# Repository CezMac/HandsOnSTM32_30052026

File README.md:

# HandsOnSTM32_30052026
Repozytorium dla uczestników

Ćwiczenie 0 - Jak używać STM32CubeProgrammera

Ćwiczenie 1 - Rozpoczęcie nowego projektu i implementacja printf()

Ćwiczenie 2 - Projekt zegarka binarnego

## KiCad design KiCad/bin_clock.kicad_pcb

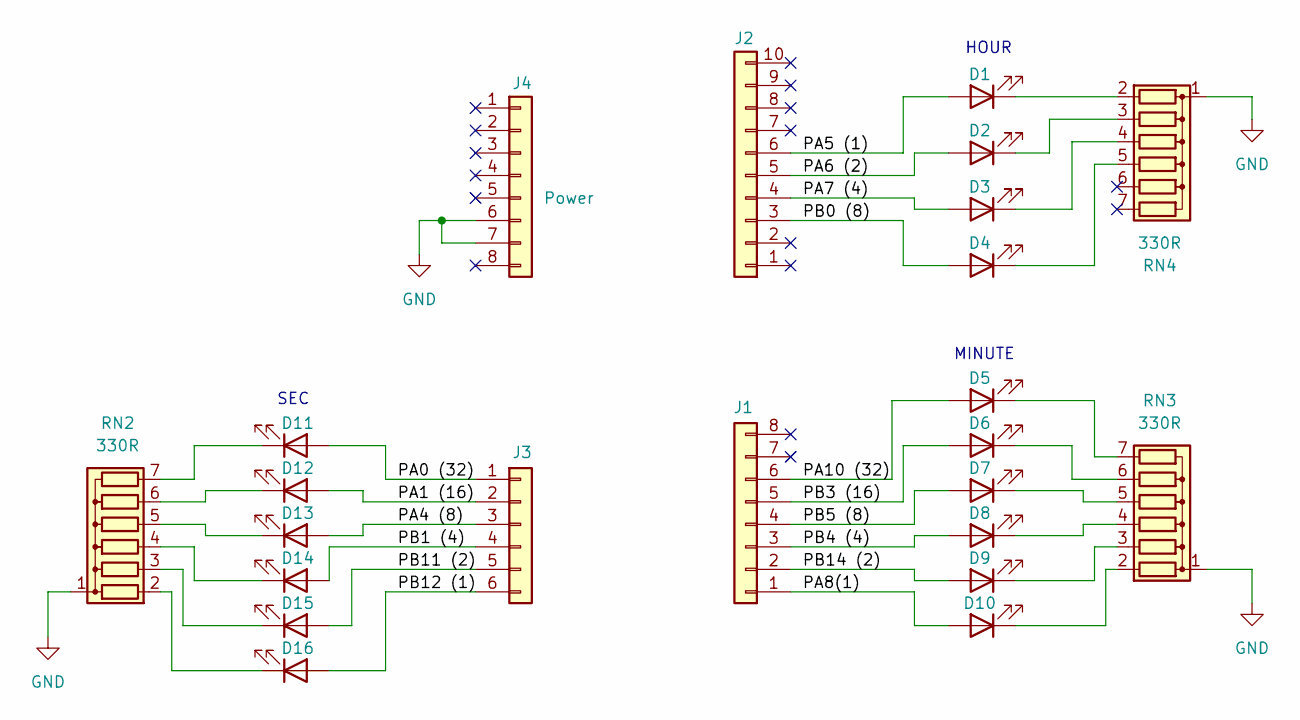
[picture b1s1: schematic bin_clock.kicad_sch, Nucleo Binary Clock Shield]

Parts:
D1, D2, D3, D4, D5, D6, D7, D8, D9, D10, D11, D12, D13, D14, D15, D16: LED; LED_D3.0mm
J1: SECONDS; PinHeader_1x08_P2.54mm_Vertical
J2: MINUTE; PinHeader_1x10_P2.54mm_Vertical
J3: Analog In; PinHeader_1x06_P2.54mm_Vertical
J4: Power; PinHeader_1x08_P2.54mm_Vertical
RN2, RN3, RN4: 330R; R_Array_SIP7

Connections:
GND: J4.6, J4.7, RN2.1 (common), RN3.1 (common), RN4.1 (common); also elsewhere on the board
unnamed: D1.2 (A), J2.6
unnamed 2: D1.1 (K), RN4.2 (R1); also elsewhere on the board
unnamed: D2.2 (A), J2.5
unnamed 4: D2.1 (K), RN4.3 (R2); also elsewhere on the board
unnamed: D3.2 (A), J2.4
unnamed 6: D3.1 (K), RN4.4 (R3); also elsewhere on the board
unnamed: D4.2 (A), J2.3
unnamed 8: D4.1 (K), RN4.5 (R4); also elsewhere on the board
unnamed: D5.2 (A), J1.6
unnamed: D5.1 (K), RN3.7 (R6)
unnamed: D6.2 (A), J1.5
unnamed: D6.1 (K), RN3.6 (R5)
unnamed: D7.2 (A), J1.4
unnamed: D7.1 (K), RN3.5 (R4)
unnamed: D8.2 (A), J1.3
unnamed: D8.1 (K), RN3.4 (R3)
unnamed: D9.2 (A), J1.2
unnamed: D9.1 (K), RN3.3 (R2)
unnamed: D10.2 (A), J1.1
unnamed: D10.1 (K), RN3.2 (R1)
unnamed: D11.2 (A), J3.1
unnamed: D11.1 (K), RN2.7 (R6)
unnamed: D12.2 (A), J3.2
unnamed: D12.1 (K), RN2.6 (R5)
unnamed: D13.2 (A), J3.3
unnamed: D13.1 (K), RN2.5 (R4)
unnamed: D14.2 (A), J3.4
unnamed: D14.1 (K), RN2.4 (R3)
unnamed: D15.2 (A), J3.5
unnamed: D15.1 (K), RN2.3 (R2)
unnamed: D16.2 (A), J3.6
unnamed: D16.1 (K), RN2.2 (R1)

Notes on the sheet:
MINUTE
SEC
HOUR

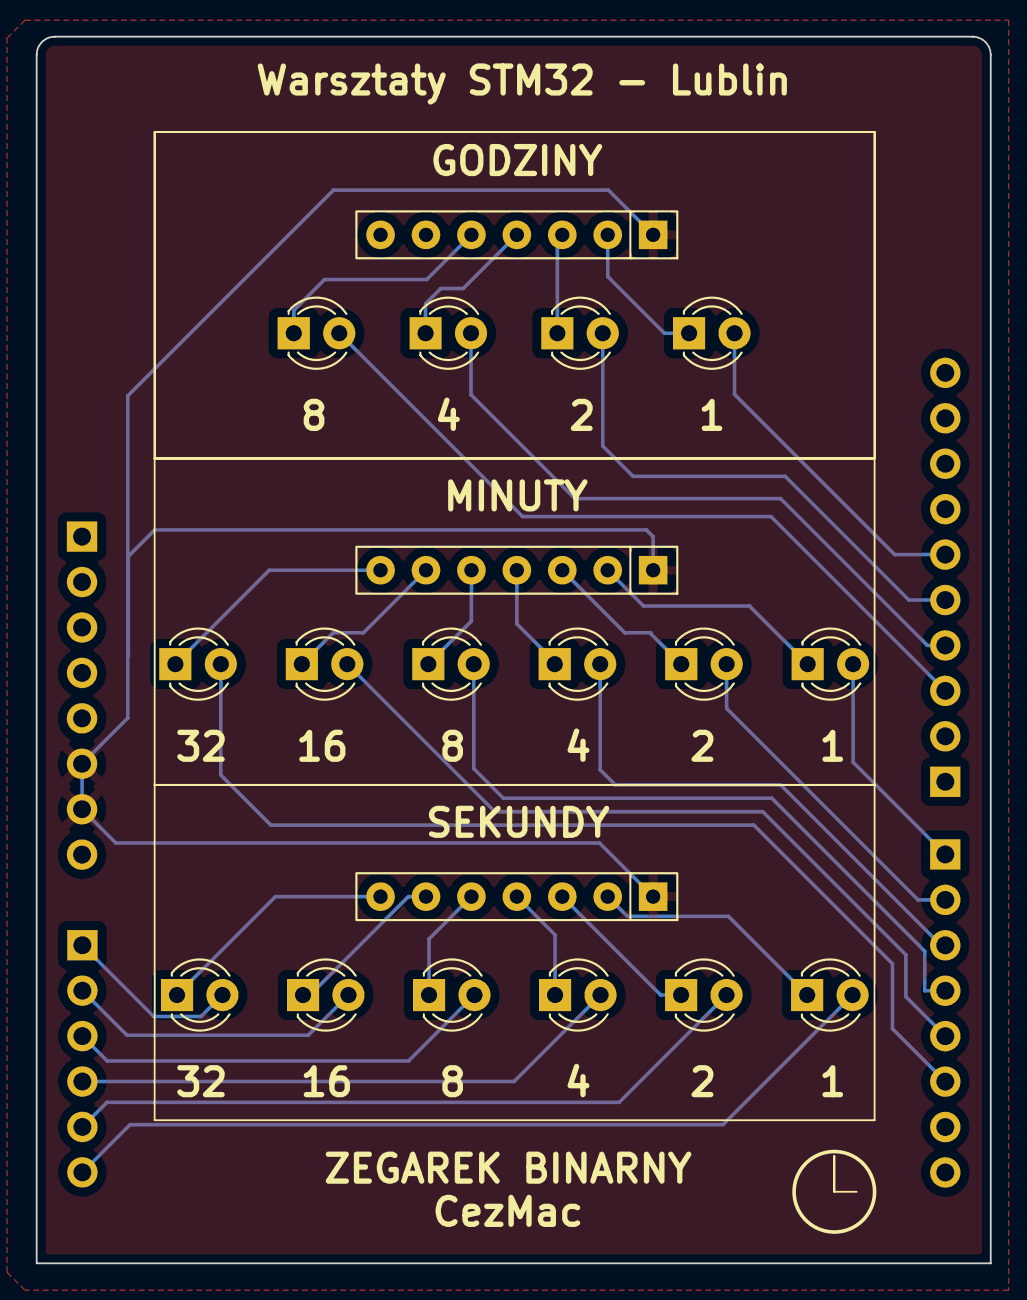
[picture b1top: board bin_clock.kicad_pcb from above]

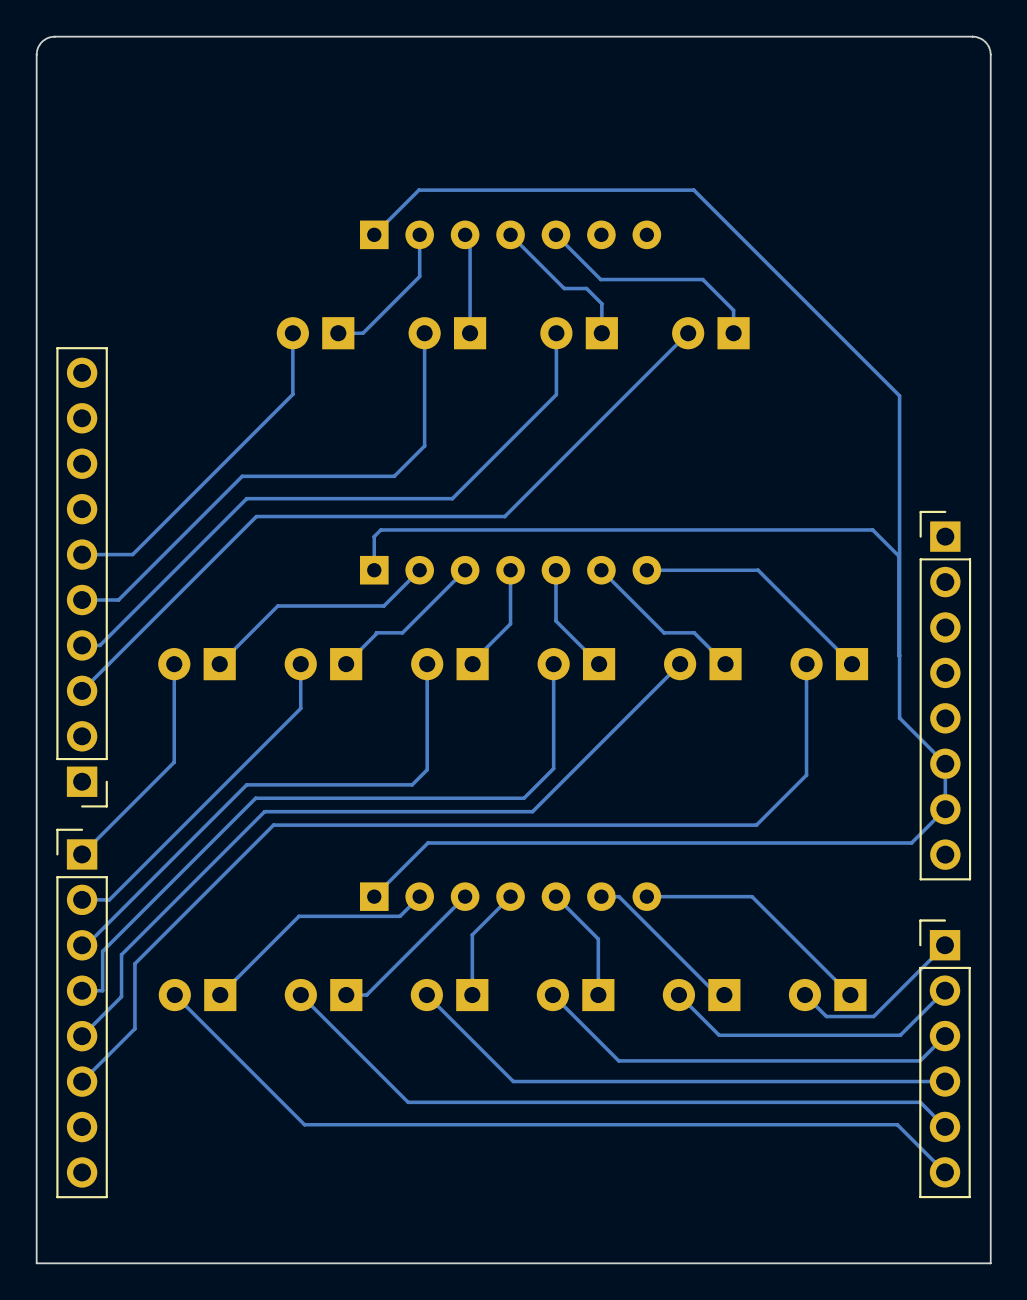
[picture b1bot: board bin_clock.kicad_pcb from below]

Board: 2 copper layers, 53.3 x 68.6 mm, 23 parts (4 on the bottom side), 33 nets.

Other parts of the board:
RN1: R_Network06; R_Array_SIP7

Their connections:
GND: RN1.1 (common); also elsewhere on the board
unnamed 2: RN1.2 (R1); also elsewhere on the board
unnamed 4: RN1.3 (R2); also elsewhere on the board
unnamed 6: RN1.4 (R3); also elsewhere on the board
unnamed 8: RN1.5 (R4); also elsewhere on the board

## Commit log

2026-05-28 Init
    Init commit
2026-05-28 Add section for Exercise 1 in READMEUpdate
2026-05-28 Update v2
2026-05-29 Update
    Update description and hex
2026-05-30 Add presentation
